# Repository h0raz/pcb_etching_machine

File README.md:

pcb_etching_machine
===================

This projekt was inspired by [this idea](http://avr-projekte.de/aetz2.htm) from Jürgen Woetzel

Though I wanted to play with servos and had some ideas I wanted to try so I wrote my own firmware and changed the hardware a little bit.
The result has some improvements and some drawbacks

It's powerded by two connectors from a computer power supply(NT in my case)
The second one is used for heating(12V) and servo(5V) because I had some issues with the sudden current changes

This machine is in use from time to time but I wouldn't say it's finished

The sizes for the plexi can be found in the construction folder, I created the file with FreeCAD

> **Features:**
> 
> - Timebased etching/exposing a pcb
> - endless etching/exposing
> - Wait for etching until temp is okay
> - Change settings during etching(etching won't stop)
> - Solid connection between heater and container
> - able to store values in EEPROM
> - menu accessible trough rotary encoder
> - servo speed adjustable and increase/decrease on startup/end

> **Todo/Bugs:**
> 
> - If temperature sensor doesn't answer program resets(atm no timeout)
    watchdog resets and shows on display so no damage should occur
> - some code cleanup and add some comments
> - heating takes somewhat long but I think it's a problem with my power supply
> - PCB needs some improvements: connectors position, enable switch board for external exposer
> - Alarm needs to be tweaked and inclued in HW

> **Things I would change if I built it again**
> 
> - use one servo or let both face the same direction
> - make the aluminium heat plate thinner

There are two holes in the heat-plate and a plate sticked to the container for the actual PCB both 3mm thick
which has two threads with short M3 screws in it so it won't move( will append some images soon)

The other screws are mostly M4 but it depends mainly on the hinges and what you have lying arround

I used some of heat foil available at Reichelt [like this](http://www.reichelt.de/THF-65100/3/index.html?&ACTION=3&LA=446&ARTICLE=108461&artnr=THF-65100&SEARCH=heizung)

If interested I can put toghether a complete list of things needed

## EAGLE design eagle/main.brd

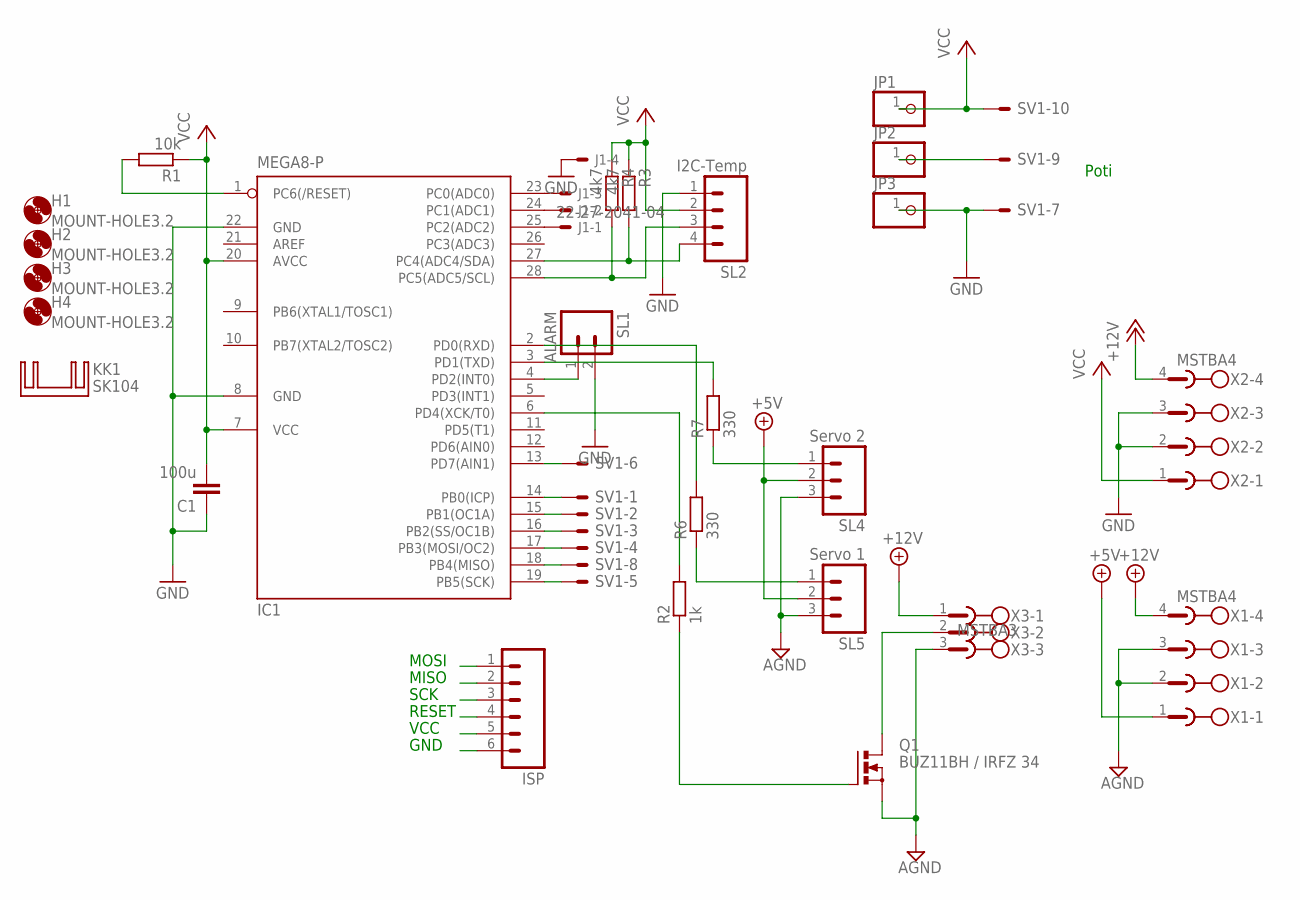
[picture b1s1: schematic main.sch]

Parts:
C1: 100u; C025-030X050
H1, H2, H3, H4: MOUNT-HOLE3.2; 3,2
IC1: MEGA8-P; DIL28-3
ISP: M06; 06P
J1: 22-27-2041-04; 6410-04
JP1, JP2, JP3: PINHD-1X1; 1X01
KK1: SK104
Q1: BUZ11BH / IRFZ 34; TO220BH
R1: 10k; 0207/10
R2: 1k; 0207/10
R3, R4: 4k7; 0207/10
R6: 330; 0207/10
R7: 330; 0207/12
SL1: ALARM; 02P
SL2: I2C-Temp; 04P
SL4: Servo 2; 03P
SL5: Servo 1; 03P
SV1: ML10E; ML10
X1, X2: MSTBA4
X3: MSTBA3

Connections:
+5V: SL4.2, SL5.2, X1.1
+12V1: X2.4
+12V2: X1.4, X3.1
AGND: Q1.S, SL4.3, SL5.3, X1.2, X1.3, X3.3
GND: C1.1, IC1.8 (GND), IC1.22 (GND), ISP.6, J1.4, JP3.1, SL1.2, SL2.1, SV1.7, X2.2, X2.3
MISO: IC1.18 (PB4(MISO)), ISP.2, SV1.8
MOSI: IC1.17 (PB3(MOSI/OC2)), ISP.1, SV1.4
unnamed: IC1.23 (PC0(ADC0)), J1.3
unnamed: IC1.15 (PB1(OC1A)), SV1.2
unnamed: IC1.16 (PB2(SS/OC1B)), SV1.3
unnamed: IC1.28 (PC5(ADC5/SCL)), R4.2, SL2.3
unnamed: IC1.27 (PC4(ADC4/SDA)), R3.2, SL2.4
unnamed: Q1.D, X3.2
unnamed: Q1.G, R2.1
unnamed: IC1.14 (PB0(ICP)), SV1.1
unnamed: JP2.1, SV1.9
unnamed: IC1.2 (PD0(RXD)), R6.2
unnamed: IC1.6 (PD4(XCK/T0)), R2.2
unnamed: R6.1, SL5.1
unnamed: R7.1, SL4.1
unnamed: IC1.24 (PC1(ADC1)), J1.2
unnamed: IC1.25 (PC2(ADC2)), J1.1
unnamed: IC1.4 (PD2(INT0)), SL1.1
unnamed: IC1.13 (PD7(AIN1)), SV1.6
unnamed: IC1.3 (PD1(TXD)), R7.2
RESET: IC1.1 (PC6(/RESET)), ISP.4, R1.2
SCK: IC1.19 (PB5(SCK)), ISP.3, SV1.5
VCC: C1.2, IC1.7 (VCC), IC1.20 (AVCC), ISP.5, JP1.1, R1.1, R3.1, R4.1, SL2.2, SV1.10, X2.1

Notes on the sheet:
GND
VCC
MOSI
MISO
SCK
RESET
Poti

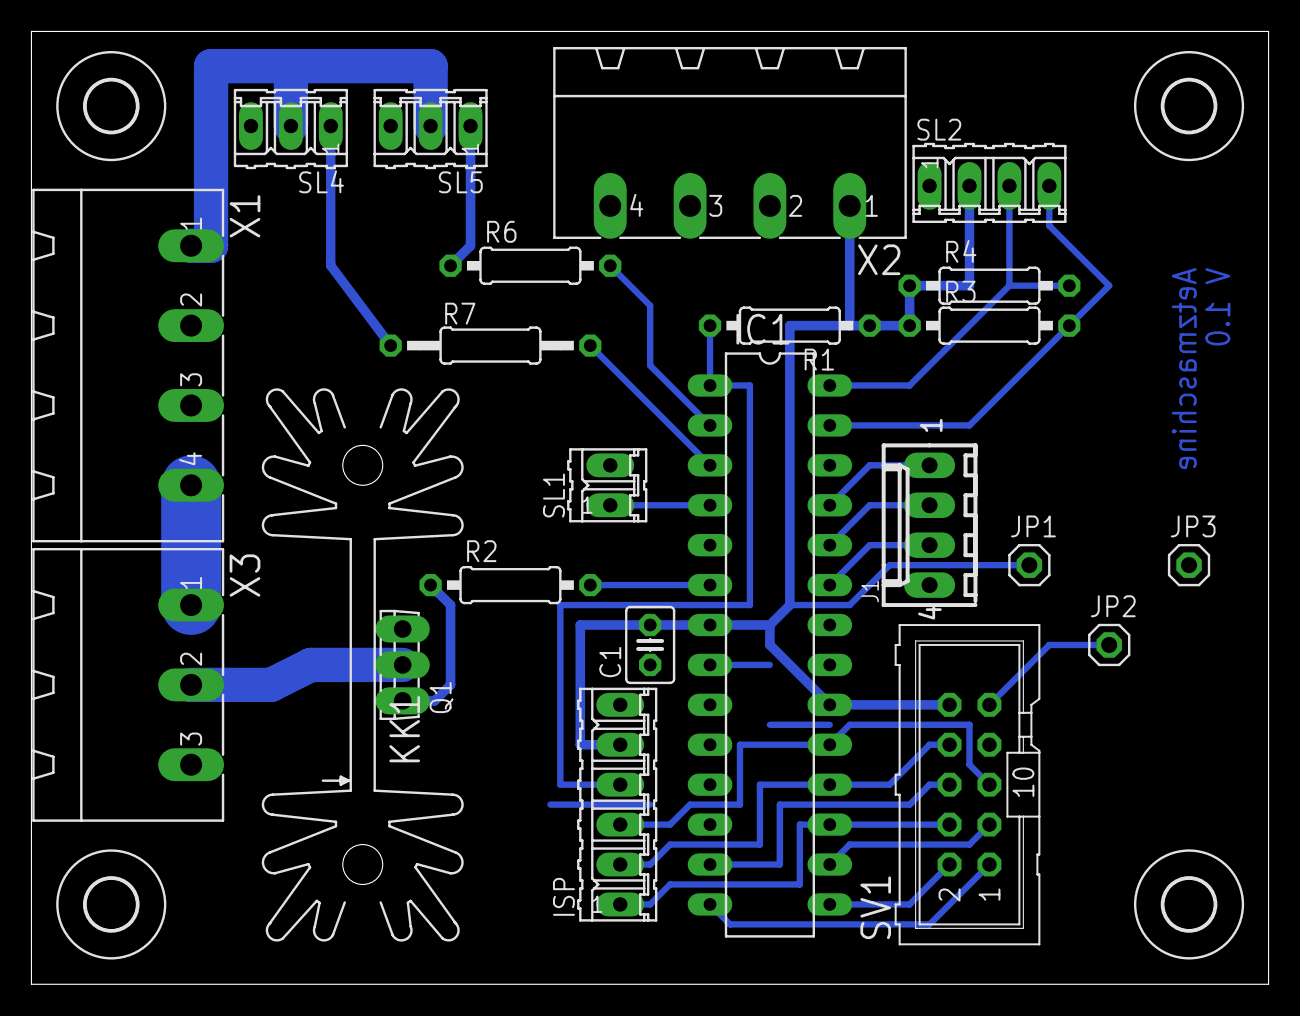
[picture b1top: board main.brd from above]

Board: 2 copper layers, 78.7 x 60.6 mm, 27 parts (0 on the bottom side), 27 nets.

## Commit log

2014-02-27 contend
2014-02-27 init data
